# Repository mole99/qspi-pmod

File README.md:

# QSPI Pmod

A QSPI Pmod board designed in KiCad with one SPI Flash and two PSRAMs.

# Pinout

| Pmod  | TinyTapeout | Function    | Note |
|-------|-------------|-------------|------|
| PMOD1 | uio[0]      | CS0 (Flash) | Cut trace to disable (see below) |
| PMOD2 | uio[1]      | SD0/MOSI    |      |
| PMOD3 | uio[2]      | SD1/MISO    |      |
| PMOD4 | uio[3]      | SCK         | Short `CK` ("CLOCK cap") pin pair for delay by 22pF cap |
| PMOD5 | uio[4]      | SD2         |      |
| PMOD6 | uio[5]      | SD3         |      |
| PMOD7 | uio[6]      | CS1 (RAM A) | Cut trace to disable (see below) |
| PMOD8 | uio[7]      | CS2 (RAM B) | Cut trace to disable (see below) |

> [!NOTE]
> On the bottom side of the PCB, you can cut the traces for any of the 3 CS pins to disable its respective memory IC. When cut, a 1k resistor pulls up the chip's `/CS` to disable it. In this case, the respective pin could be used (via header thru-hole on the other side of the cut) as either an input or output.

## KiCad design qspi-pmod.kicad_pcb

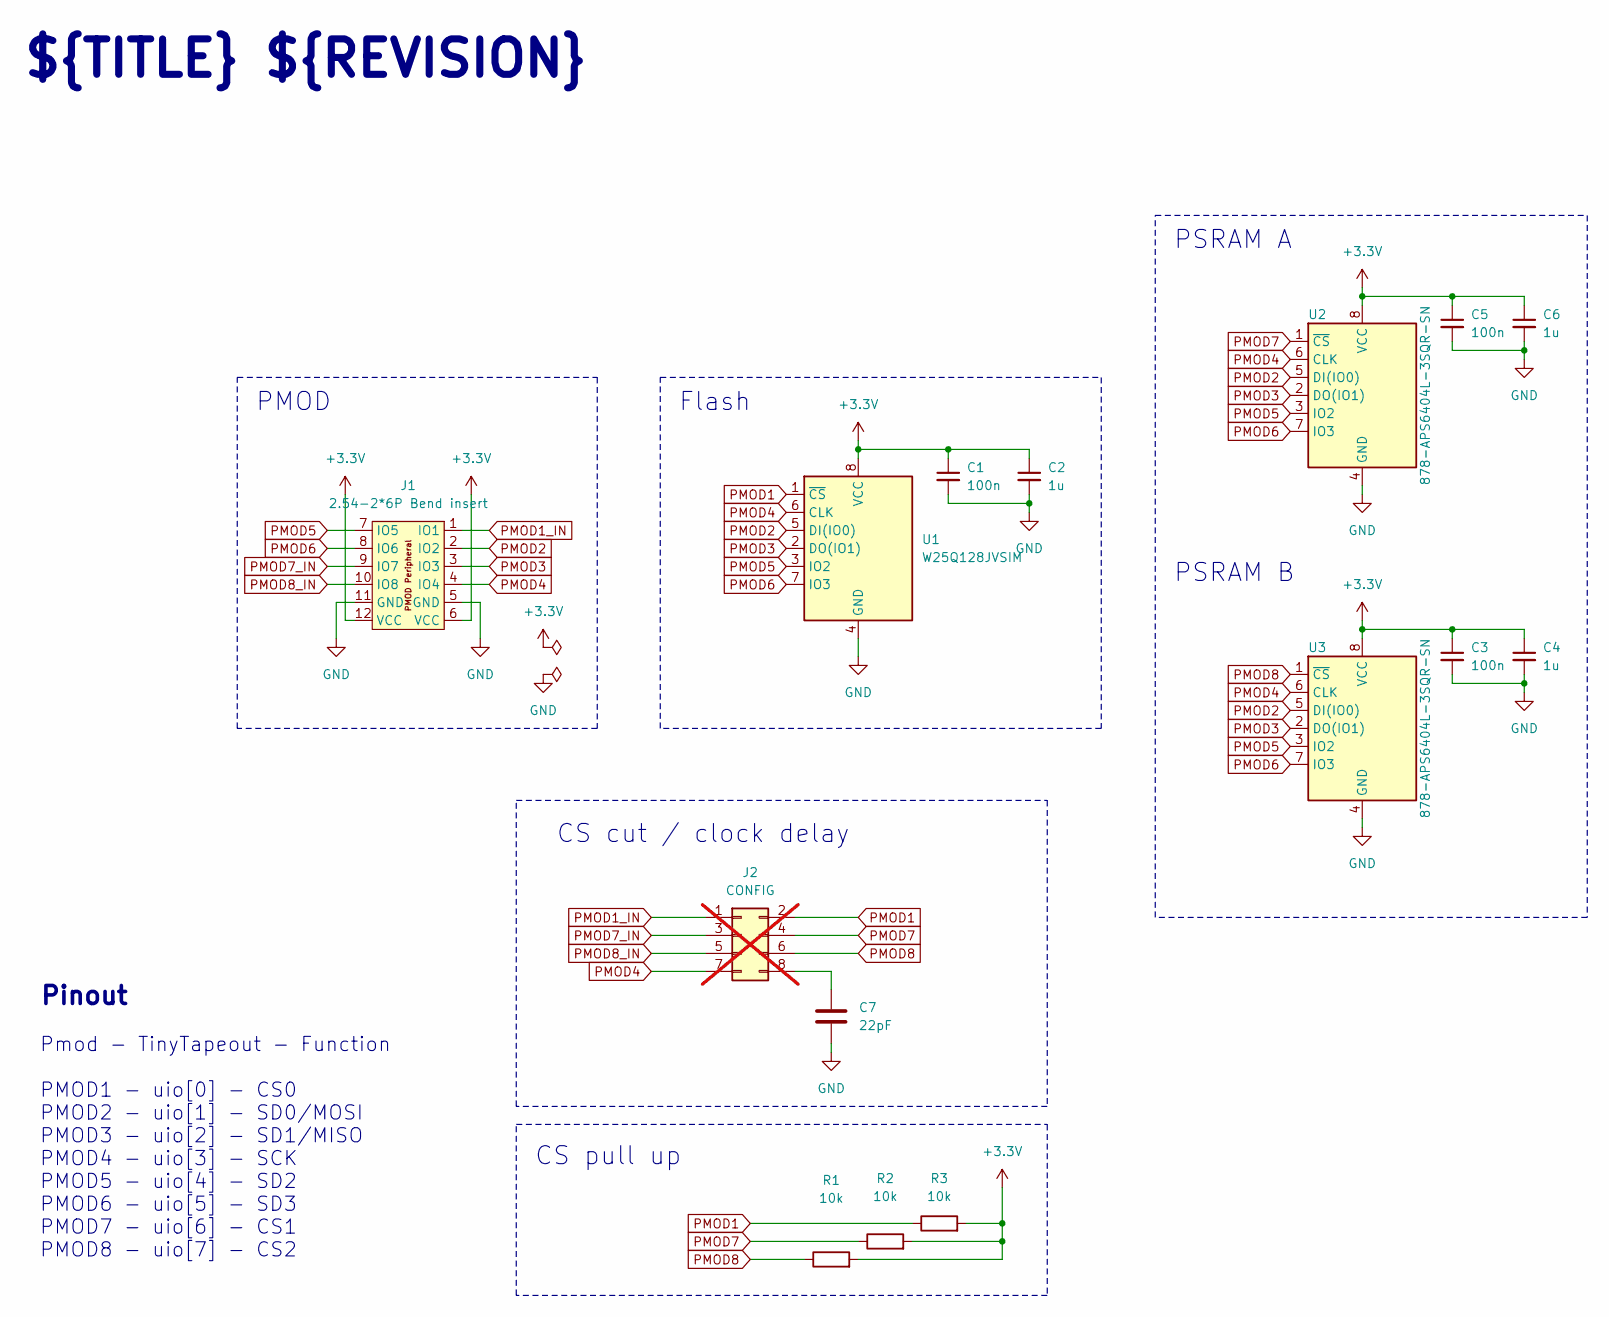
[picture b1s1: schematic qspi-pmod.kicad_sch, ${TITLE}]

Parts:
C1, C3, C5: 100n; C_0402_1005Metric; MPN 0402YC104KAT2A
C2, C4, C6: 1u; C_0402_1005Metric; MPN C0402C105M9PAC
C7: 22pF; C_0402_1005Metric; MPN 0402CG220J500NT
J1: 2.54-2*6P Bend insert; PinHeader_2x06_P2.54mm_PMODPeriph2B; MPN 2.54-2*6P; LCSC Part C60565
J2: CONFIG; PinHeader_2x04_P2.54mm_Vertical; not fitted
R1, R2, R3: 10k; R_0402_1005Metric; MPN 0402WGF1002TCE
U1: W25Q128JVSIM; SOIC-8_5.23x5.23mm_P1.27mm; MPN W25Q128JVSIM
U2, U3: 878-APS6404L-3SQR-SN; SOP-8_3.9x4.9mm_P1.27mm; MPN APS6404L-3SQR-SN

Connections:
+3.3V: C1.1, C2.1, C3.1, C4.1, C5.1, C6.1, J1.6 (VCC), J1.12 (VCC), R1.2, R2.2, R3.2, U1.8 (VCC), U2.8 (VCC), U3.8 (VCC)
GND: C1.2, C2.2, C3.2, C4.2, C5.2, C6.2, C7.1, J1.5 (GND), J1.11 (GND), U1.4 (GND), U2.4 (GND), U3.4 (GND)
unnamed: C7.2, J2.8
PMOD1: J2.2, R3.1, U1.1 (~CS)
PMOD1_IN: J1.1 (IO1), J2.1
PMOD2: J1.2 (IO2), U1.5 (DI(IO0)), U2.5 (DI(IO0)), U3.5 (DI(IO0))
PMOD3: J1.3 (IO3), U1.2 (DO(IO1)), U2.2 (DO(IO1)), U3.2 (DO(IO1))
PMOD4: J1.4 (IO4), J2.7, U1.6 (CLK), U2.6 (CLK), U3.6 (CLK)
PMOD5: J1.7 (IO5), U1.3 (IO2), U2.3 (IO2), U3.3 (IO2)
PMOD6: J1.8 (IO6), U1.7 (IO3), U2.7 (IO3), U3.7 (IO3)
PMOD7: J2.4, R2.1, U2.1 (~CS)
PMOD7_IN: J1.9 (IO7), J2.3
PMOD8: J2.6, R1.1, U3.1 (~CS)
PMOD8_IN: J1.10 (IO8), J2.5

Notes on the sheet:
CS cut / clock delay
PMOD
Flash
PSRAM B
CS pull up
${TITLE} ${REVISION}
PSRAM A
Pmod - TinyTapeout - Function PMOD1 - uio[0] - CS0 PMOD2 - uio[1] - SD0/MOSI PMOD3 - uio[2] - SD1/MISO PMOD4 - uio[3] - SCK PMOD5 - uio[4] - SD2 PMOD6 - uio[5] - SD3 PMOD7 - uio[6] - CS1 PMOD8 - uio[7] - CS2
Pinout

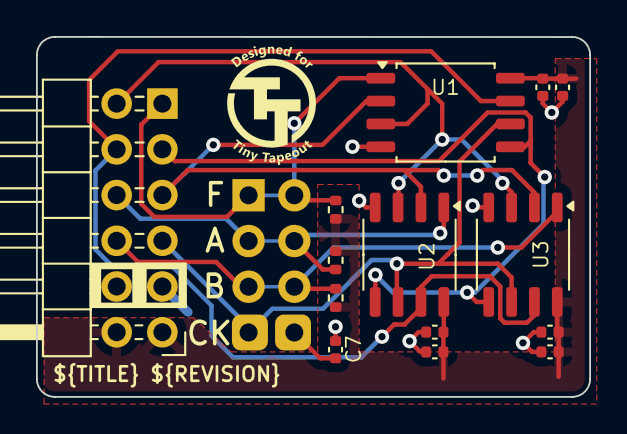
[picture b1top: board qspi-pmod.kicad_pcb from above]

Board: 2 copper layers, 30.7 x 20.0 mm, 15 parts (0 on the bottom side), 14 nets.

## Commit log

2023-11-11 Push schematic and board
2023-11-11 Add 3D models
2023-12-09 Finish routing
2023-12-09 Fixup
2024-01-25 Apply minimum copper to edge clearance
2024-08-07 Add optional CLK cap and CS disconnects
2024-08-08 A few small tweaks
2024-08-08 Part numbers
2024-08-09 Add image to README
2024-08-09 Use text variables
2024-08-09 Change cap to 22pF
2024-08-12 BOM updates
2024-11-01 Clarify CS pin functions
2024-11-05 Update README re CS/cap traces and v2.1 board pic top/bottom
2024-11-05 Minor corrections to README
2025-09-19 Make pull ups 10k
2026-02-18 fix: correct braces in fp-lib-table
